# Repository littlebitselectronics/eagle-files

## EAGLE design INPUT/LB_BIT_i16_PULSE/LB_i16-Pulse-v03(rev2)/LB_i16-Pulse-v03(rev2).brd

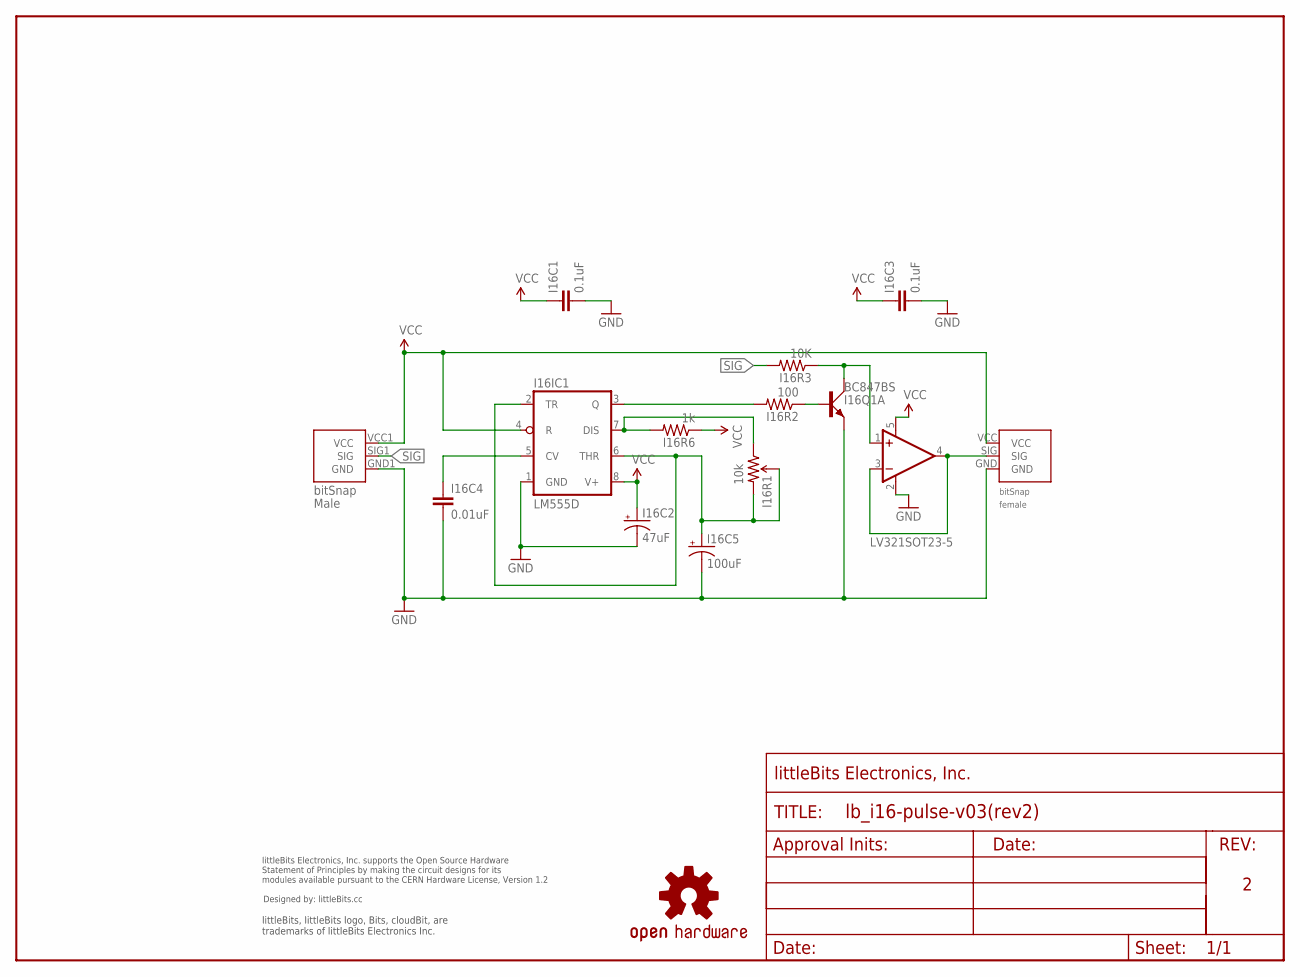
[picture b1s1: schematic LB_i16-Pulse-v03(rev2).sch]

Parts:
I16BSF1: BITSNAP_V03_FEMALE
I16BSM1: BITSNAP_V03_MALE
I16C1, I16C3: 0.1uF; 0603-CAP
I16C2: 47uF; EIA3528
I16C4: 0.01uF; 0603-CAP
I16C5: 100uF; EIA6032
I16IC1: LM555D; SO08
I16Q1: BC847BS; SOT363_PHILIPS
I16R1: 10k; TRIMPOT-3MM
I16R2: 100; 0603-RES
I16R3: 10K; 0603-RES
I16R6: 1k; 0603-RES
I16U3: LV321SOT23-5; SOT23-5
U$1: OSHWCREDIT
U$2: FRAME-LETTER-OHWOHW; FABDWG01-OHW
U$3: OSHW-LOGOL; OSHW-LOGO-L

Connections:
GND: I16BSF1.GND, I16BSM1.GND1 (GND), I16C1.2, I16C2.C (-), I16C3.2, I16C4.2, I16C5.P$2 (-), I16IC1.1 (GND), I16Q1.1 (E), I16U3.2 (V-)
unnamed: I16Q1.6 (C), I16R3.1, I16U3.1 (+IN)
unnamed: I16BSF1.SIG, I16U3.3 (-IN), I16U3.4 (OUT)
unnamed: I16IC1.3 (Q), I16R2.2
unnamed: I16Q1.2 (B), I16R2.1
unnamed: I16C4.1, I16IC1.5 (CV)
unnamed: I16IC1.7 (DIS), I16R1.1 (CCW), I16R6.2
unnamed: I16C5.P$1 (+), I16IC1.2 (TR), I16IC1.6 (THR), I16R1.2 (WIPER), I16R1.3 (CW)
SIG: I16BSM1.SIG1 (SIG), I16R3.2
VCC: I16BSF1.VCC, I16BSM1.VCC1 (VCC), I16C1.1, I16C2.A (+), I16C3.1, I16IC1.4 (R), I16IC1.8 (V+), I16R6.1, I16U3.5 (V+)

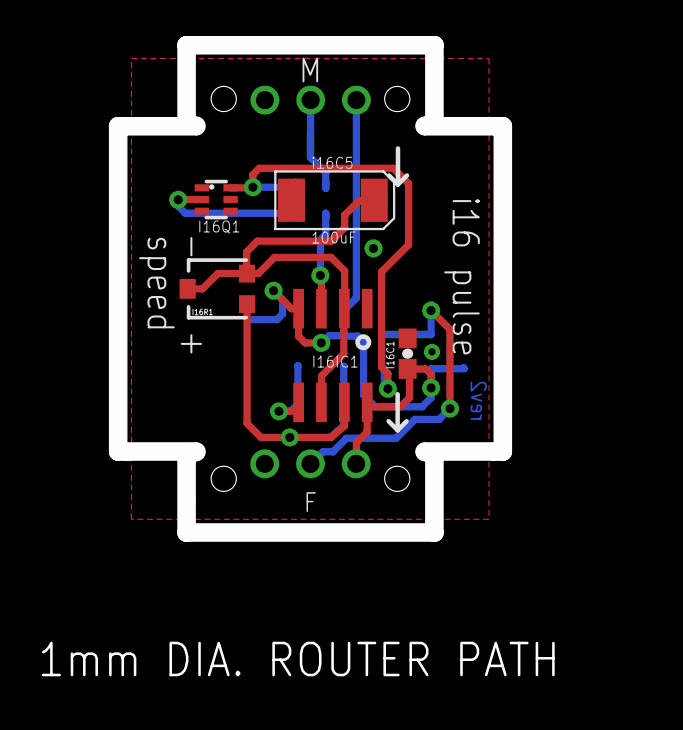
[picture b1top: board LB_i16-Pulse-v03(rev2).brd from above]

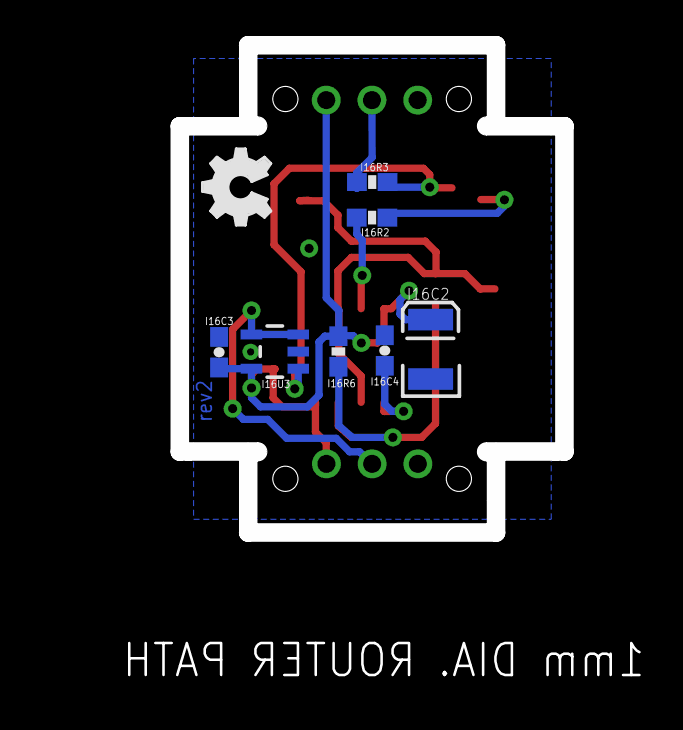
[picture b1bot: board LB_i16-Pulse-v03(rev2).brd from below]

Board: 2 copper layers, 21.4 x 27.1 mm, 18 parts (7 on the bottom side), 10 nets.

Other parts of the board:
U$20: OSHW_FILLX150_NOTEXT

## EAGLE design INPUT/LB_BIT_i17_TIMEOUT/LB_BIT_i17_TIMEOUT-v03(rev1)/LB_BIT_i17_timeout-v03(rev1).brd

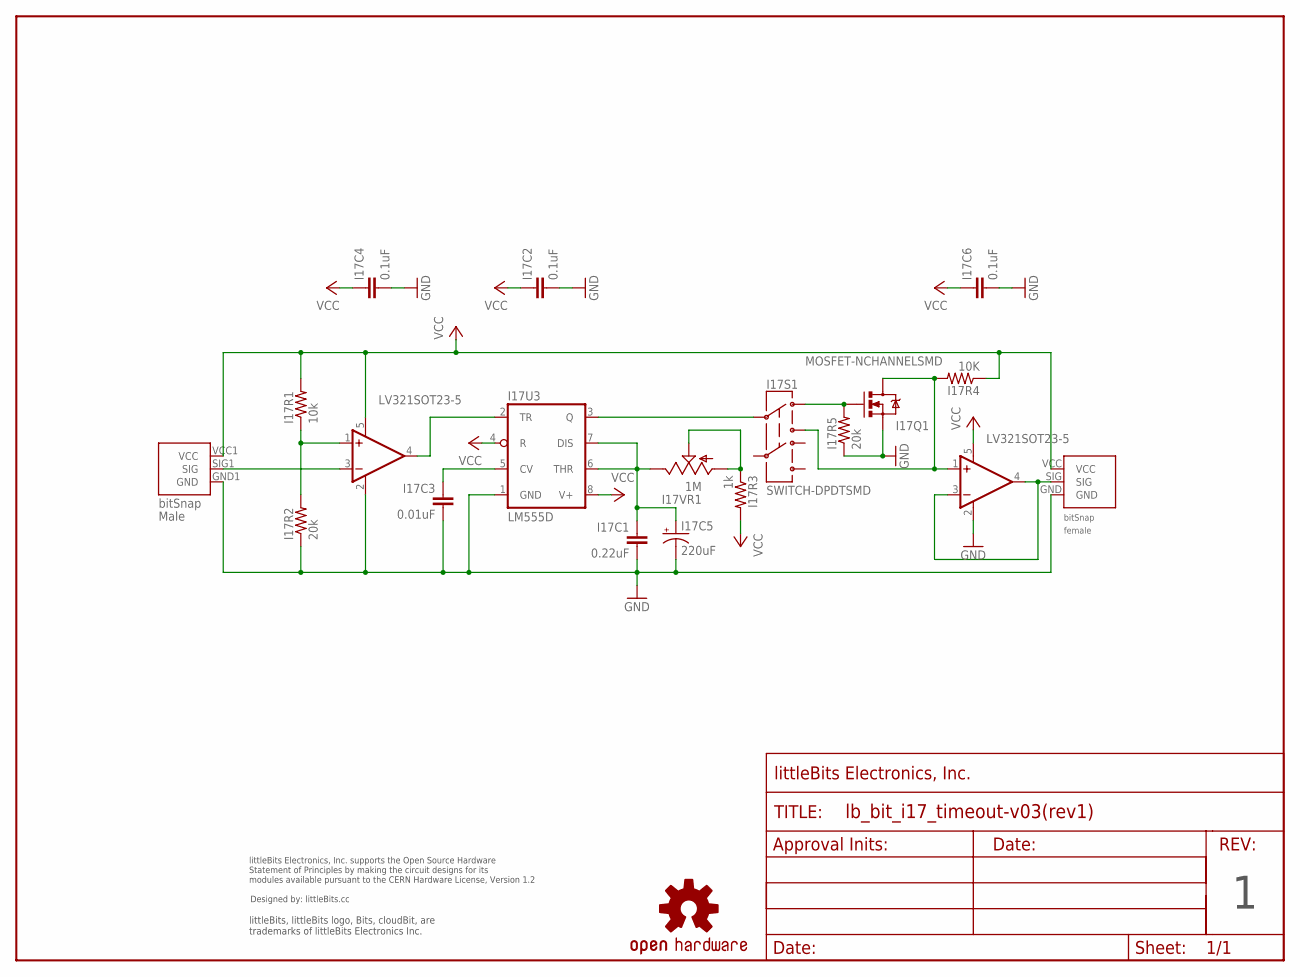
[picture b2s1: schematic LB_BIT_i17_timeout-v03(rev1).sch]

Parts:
I17BSF1: BITSNAP_V03_FEMALE
I17BSM1: BITSNAP_V03_MALE
I17C1: 0.22uF; 0603-CAP
I17C2, I17C4, I17C6: 0.1uF; 0603-CAP
I17C3: 0.01uF; 0603-CAP
I17C5: 220uF; PANASONIC_D
I17Q1: MOSFET-NCHANNELSMD; SOT23-3
I17R1: 10k; 0603-RES
I17R2, I17R5: 20k; 0603-RES
I17R3: 1k; 0603-RES
I17R4: 10K; 0603-RES
I17S1: SWITCH-DPDTSMD; AYZ0202
I17U1, I17U2: LV321SOT23-5; SOT23-5
I17U3: LM555D; SO08
I17VR1: 1M; POT-TRIM-SMD-BOURNS-3303
U$1: OSHWCREDIT
U$2: FRAME-LETTER-OHWOHW; FABDWG01-OHW
U$4: OSHW-LOGOL; OSHW-LOGO-L

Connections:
GND: I17BSF1.GND, I17BSM1.GND1 (GND), I17C1.2, I17C2.2, I17C3.2, I17C4.2, I17C5.-, I17C6.2, I17Q1.2 (S), I17R2.1, I17R5.1, I17U1.2 (V-), I17U2.2 (V-), I17U3.1 (GND)
unnamed: I17C3.1, I17U3.5 (CV)
unnamed: I17Q1.3 (D), I17R4.2, I17S1.3, I17U2.1 (+IN)
unnamed: I17Q1.1 (G), I17R5.2, I17S1.1
unnamed: I17BSM1.SIG1 (SIG), I17U1.3 (-IN)
unnamed: I17R3.1, I17VR1.1 (A), I17VR1.2 (S)
unnamed: I17S1.2, I17U3.3 (Q)
unnamed: I17BSF1.SIG, I17U2.3 (-IN), I17U2.4 (OUT)
unnamed: I17U1.4 (OUT), I17U3.2 (TR)
unnamed: I17R1.1, I17R2.2, I17U1.1 (+IN)
unnamed: I17C1.1, I17C5.+, I17U3.6 (THR), I17U3.7 (DIS), I17VR1.3 (E)
VCC: I17BSF1.VCC, I17BSM1.VCC1 (VCC), I17C2.1, I17C4.1, I17C6.1, I17R1.2, I17R3.2, I17R4.1, I17U1.5 (V+), I17U2.5 (V+), I17U3.4 (R), I17U3.8 (V+)

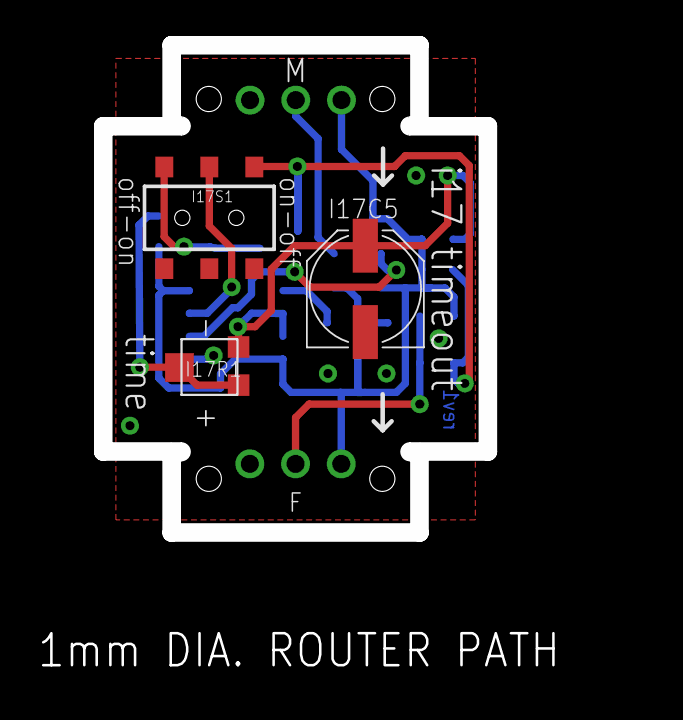
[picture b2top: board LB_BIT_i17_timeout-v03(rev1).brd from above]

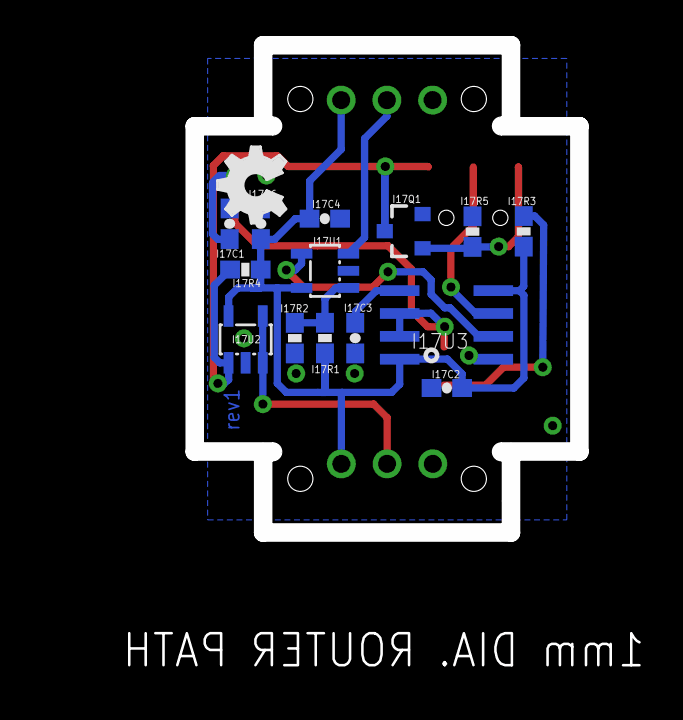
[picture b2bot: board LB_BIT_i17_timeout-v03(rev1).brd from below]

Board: 2 copper layers, 21.4 x 27.1 mm, 23 parts (14 on the bottom side), 12 nets.

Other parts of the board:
U$6: OSHW_FILLX150_NOTEXT

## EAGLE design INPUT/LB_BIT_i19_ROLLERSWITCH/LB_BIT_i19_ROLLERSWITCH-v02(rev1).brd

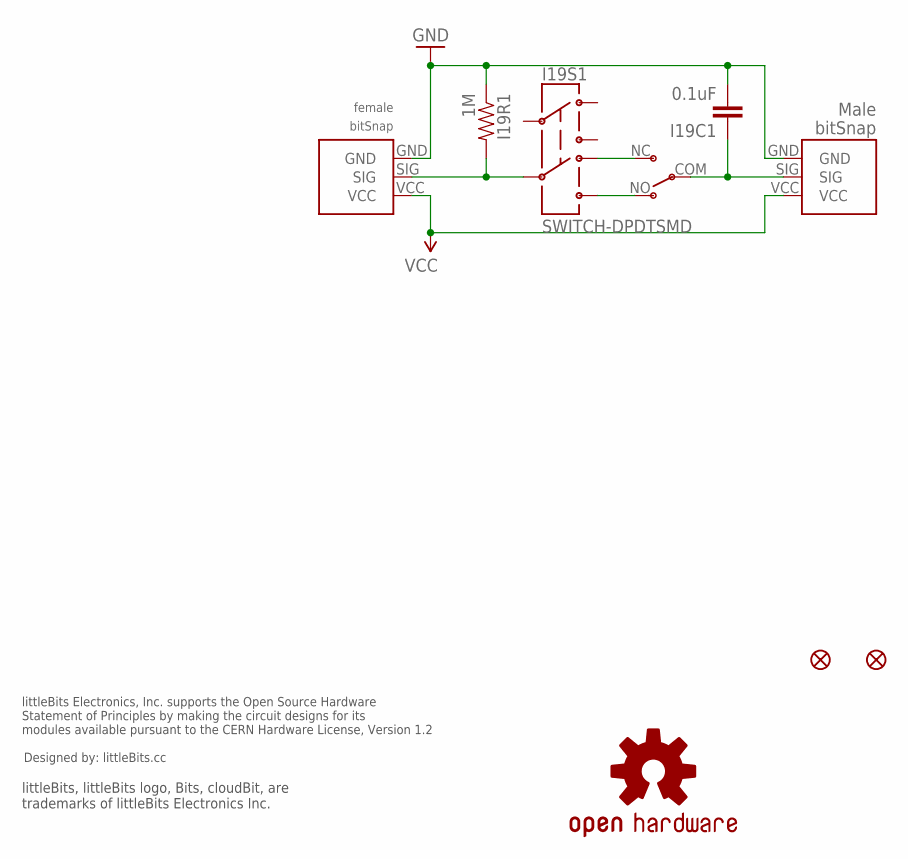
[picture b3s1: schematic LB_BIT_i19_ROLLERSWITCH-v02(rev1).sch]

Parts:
I3BSF: BITSNAP_FEMALE
I3BSM: BITSNAP_MALE
I19C1: 0.1uF; 0603-CAP
I19FD1, I19FD2: FIDUCIAL1X2; FIDUCIAL-1X2
I19R1: 1M; 0603-RES
I19S1: SWITCH-DPDTSMD; AYZ0202
I19SW2: ROLLERSWITCH-OMRON-SS-5GL2DRIGHTANGLE; ROLLERSWITCH-OMRON-D2F-01FL-A
U$1: OSHWCREDIT
U$3: OSHW-LOGOL; OSHW-LOGO-L

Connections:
GND: I3BSF.GND, I3BSM.GND, I19C1.2, I19R1.1
unnamed: I19S1.4, I19SW2.NC
unnamed: I19S1.6, I19SW2.NO
SIG: I3BSF.SIG, I19R1.2, I19S1.5
SIG2: I3BSM.SIG, I19C1.1, I19SW2.COM
VCC: I3BSF.VCC, I3BSM.VCC

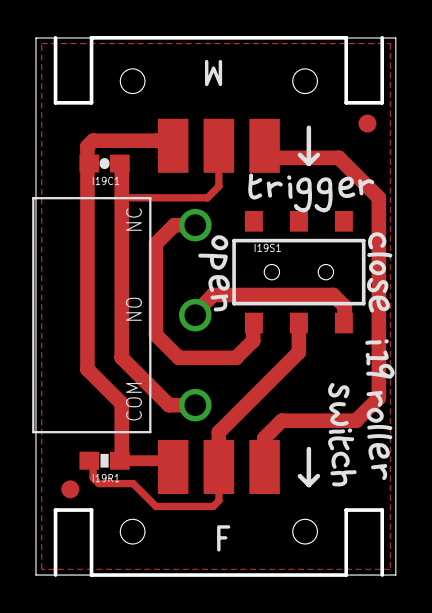
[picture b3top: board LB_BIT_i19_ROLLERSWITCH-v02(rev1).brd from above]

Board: 2 copper layers, 20.0 x 29.8 mm, 43 parts (0 on the bottom side), 6 nets.

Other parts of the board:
U$2: LB_CREDITS_V2
U$20: OSHW_FILLX150_NOTEXT
U$36, U$55: T
U$37, U$42, U$46, U$51: R
U$38, U$43, U$54: I
U$39, U$40: G
U$41, U$50, U$62, U$65: E
U$44: 1
U$45: 9
U$47, U$60, U$63: O
U$48, U$49, U$59: L
U$52, U$61: S
U$53: W
U$56, U$58: C
U$57: H
U$64: P
U$66: N

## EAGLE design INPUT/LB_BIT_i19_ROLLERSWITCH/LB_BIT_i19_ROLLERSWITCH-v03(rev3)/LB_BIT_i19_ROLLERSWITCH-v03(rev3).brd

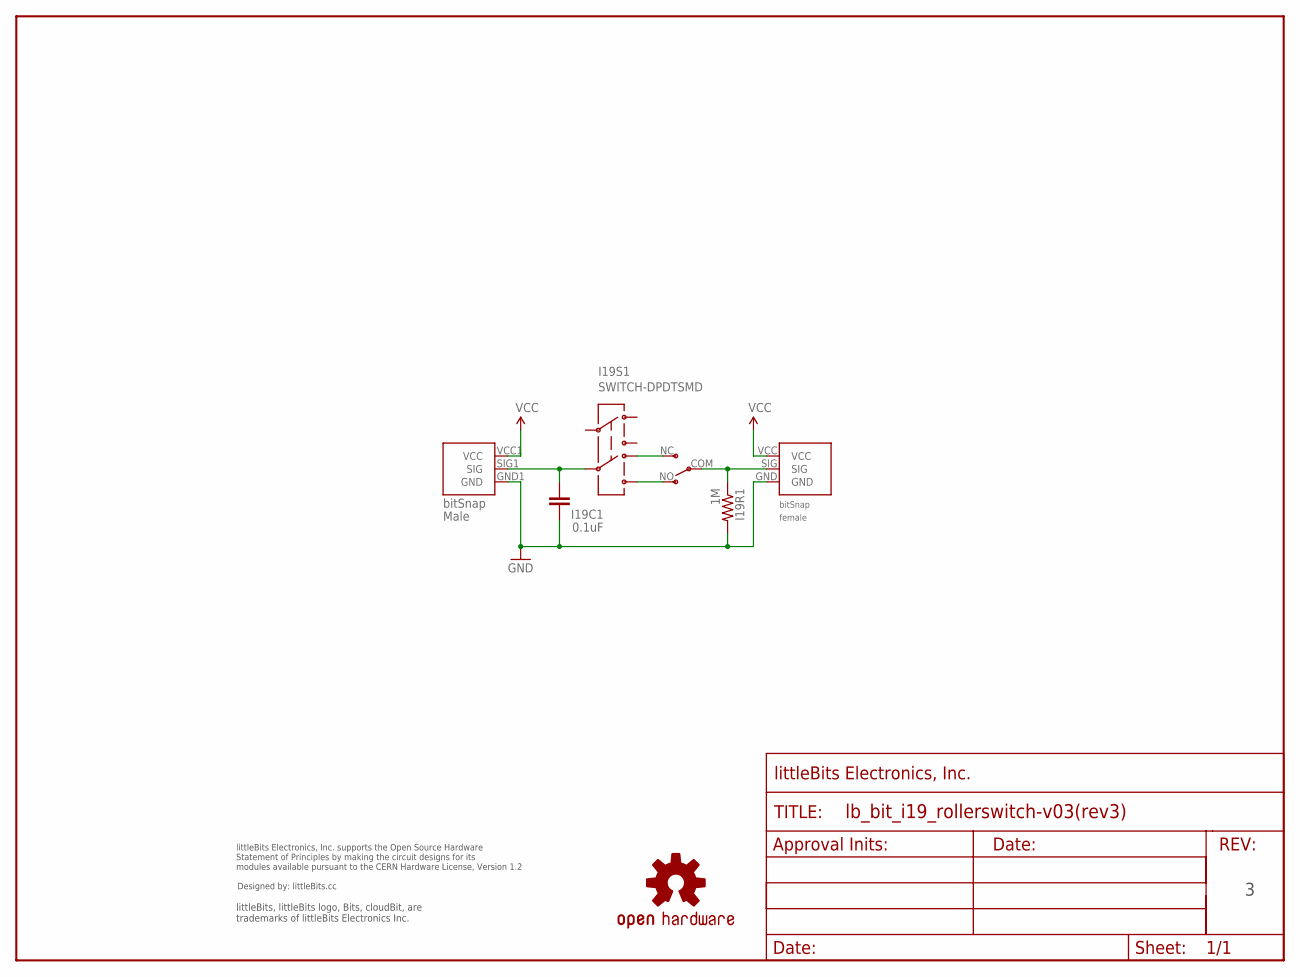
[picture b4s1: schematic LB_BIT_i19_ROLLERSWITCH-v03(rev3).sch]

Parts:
FRAME1: FRAME-LETTER-OHWOHW; FABDWG01-OHW
I19BSF1: BITSNAP_V03_FEMALE
I19BSM1: BITSNAP_V03_MALE
I19C1: 0.1uF; 0603-CAP
I19R1: 1M; 0603-RES
I19S1: SWITCH-DPDTSMD; AYZ0202
I19SW2: ROLLERSWITCH-OMRON-SS-5GL2DRIGHTANGLE; ROLLERSWITCH-OMRON-D2F-01FL-A
U$1: OSHWCREDIT
U$3: OSHW-LOGOL; OSHW-LOGO-L

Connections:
GND: I19BSF1.GND, I19BSM1.GND1 (GND), I19C1.1, I19R1.2
unnamed: I19S1.4, I19SW2.NC
unnamed: I19S1.6, I19SW2.NO
SIG: I19BSM1.SIG1 (SIG), I19C1.2, I19S1.5
SIG2: I19BSF1.SIG, I19R1.1, I19SW2.COM
VCC: I19BSF1.VCC, I19BSM1.VCC1 (VCC)

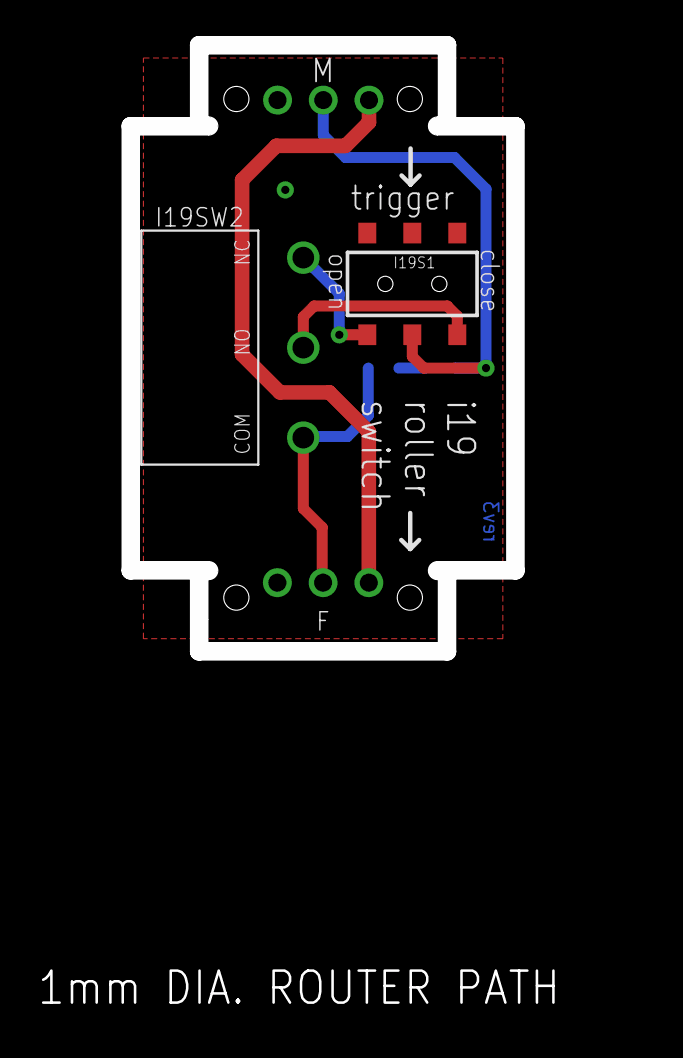
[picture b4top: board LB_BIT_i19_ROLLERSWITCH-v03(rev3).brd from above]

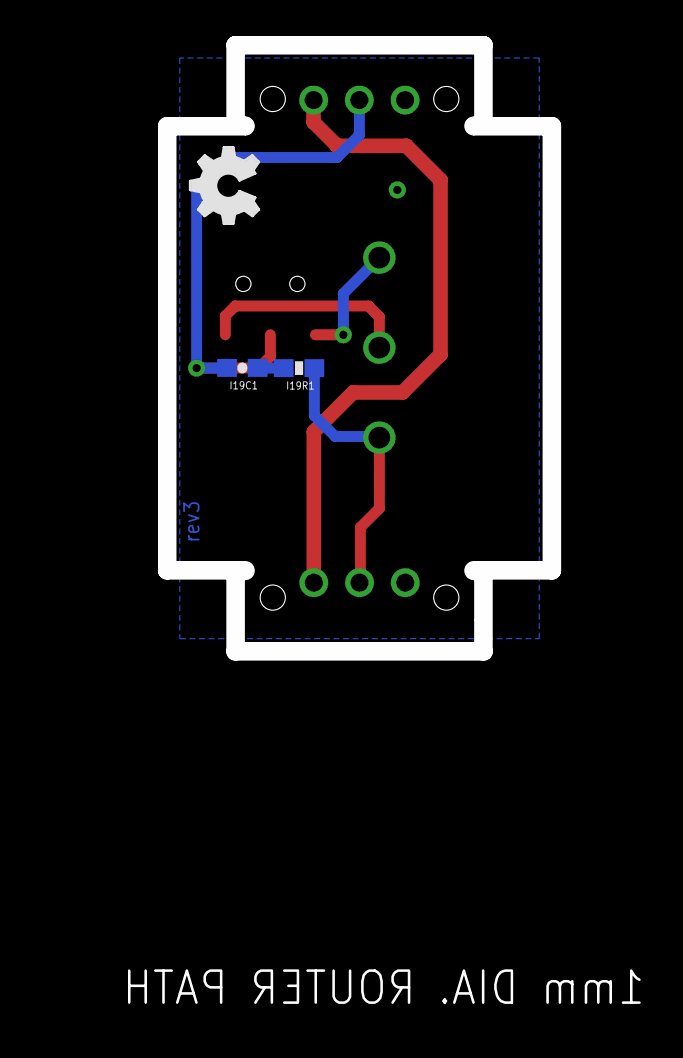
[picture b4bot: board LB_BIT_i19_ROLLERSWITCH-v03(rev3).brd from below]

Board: 2 copper layers, 21.4 x 33.7 mm, 10 parts (2 on the bottom side), 6 nets.

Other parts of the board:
U$20: OSHW_FILLX150_NOTEXT

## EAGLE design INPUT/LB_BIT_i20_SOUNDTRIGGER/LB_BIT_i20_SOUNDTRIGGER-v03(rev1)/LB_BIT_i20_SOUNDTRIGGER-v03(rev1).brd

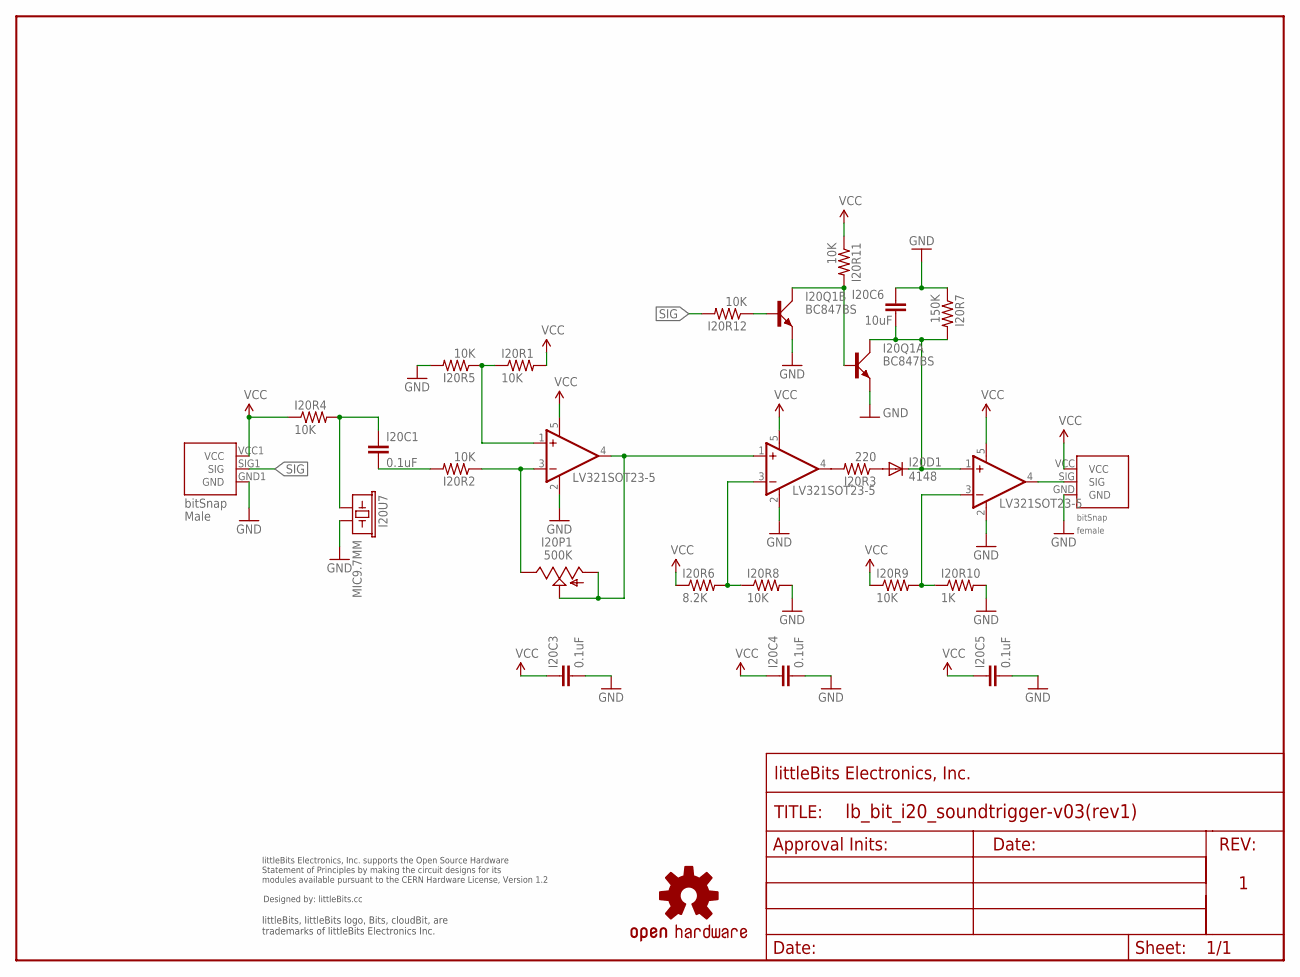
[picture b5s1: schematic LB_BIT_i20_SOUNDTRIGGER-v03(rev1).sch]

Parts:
I20BSF1: BITSNAP_V03_FEMALE
I20BSM1: BITSNAP_V03_MALE
I20C1, I20C3, I20C4, I20C5: 0.1uF; 0603-CAP
I20C6: 10uF; 0805
I20D1: 4148; SOD-323
I20P1: 500K; POT-TRIM-SMD-BOURNS-3303
I20Q1: BC847BS; SOT363_PHILIPS
I20R1, I20R2, I20R4, I20R5, I20R8, I20R9, I20R11, I20R12: 10K; 0603-RES
I20R3: 220; 0603-RES
I20R6: 8.2K; 0603-RES
I20R7: 150K; 0603-RES
I20R10: 1K; 0603-RES
I20U1, I20U2, I20U3: LV321SOT23-5; SOT23-5
I20U7: MIC9.7MM; MIC-9.7MM
U$1: OSHWCREDIT
U$5: FRAME-LETTER-OHWOHW; FABDWG01-OHW
U$29: OSHW-LOGOL; OSHW-LOGO-L

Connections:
GND: I20BSF1.GND, I20BSM1.GND1 (GND), I20C3.2, I20C4.2, I20C5.2, I20C6.1, I20Q1.1 (E), I20Q1.4 (E), I20R5.2, I20R7.1, I20R8.2, I20R10.2, I20U1.2 (V-), I20U2.2 (V-), I20U3.2 (V-), I20U7.2
unnamed: I20P1.3 (E), I20R2.1, I20U1.3 (-IN)
unnamed: I20C1.2, I20R2.2
unnamed: I20C1.1, I20R4.2, I20U7.1
unnamed: I20P1.1 (A), I20P1.2 (S), I20U1.4 (OUT), I20U2.1 (+IN)
unnamed: I20R1.1, I20R5.1, I20U1.1 (+IN)
unnamed: I20C6.2, I20D1.1 (C), I20Q1.6 (C), I20R7.2, I20U3.1 (+IN)
unnamed: I20R6.2, I20R8.1, I20U2.3 (-IN)
unnamed: I20R3.2, I20U2.4 (OUT)
unnamed: I20Q1.2 (B), I20Q1.3 (C), I20R11.2
unnamed: I20BSF1.SIG, I20U3.4 (OUT)
unnamed: I20R9.2, I20R10.1, I20U3.3 (-IN)
unnamed: I20D1.2 (A), I20R3.1
unnamed: I20Q1.5 (B), I20R12.1
SIG: I20BSM1.SIG1 (SIG), I20R12.2
VCC: I20BSF1.VCC, I20BSM1.VCC1 (VCC), I20C3.1, I20C4.1, I20C5.1, I20R1.2, I20R4.1, I20R6.1, I20R9.1, I20R11.1, I20U1.5 (V+), I20U2.5 (V+), I20U3.5 (V+)

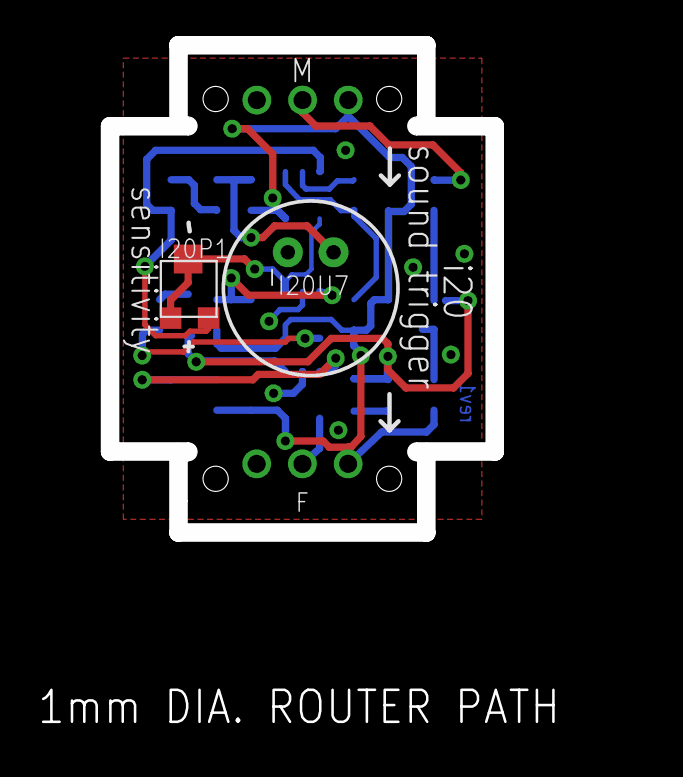
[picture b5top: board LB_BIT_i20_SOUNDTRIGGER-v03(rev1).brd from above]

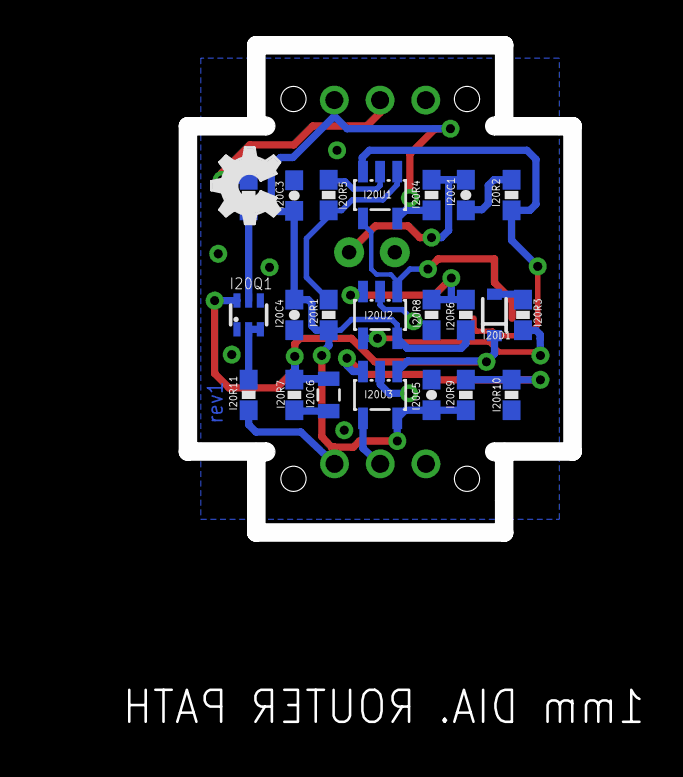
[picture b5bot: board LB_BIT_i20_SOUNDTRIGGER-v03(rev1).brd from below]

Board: 2 copper layers, 21.4 x 27.1 mm, 32 parts (22 on the bottom side), 16 nets.

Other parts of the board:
U$2: OSHW_FILLX150_NOTEXT
U$3: +
U$4: -

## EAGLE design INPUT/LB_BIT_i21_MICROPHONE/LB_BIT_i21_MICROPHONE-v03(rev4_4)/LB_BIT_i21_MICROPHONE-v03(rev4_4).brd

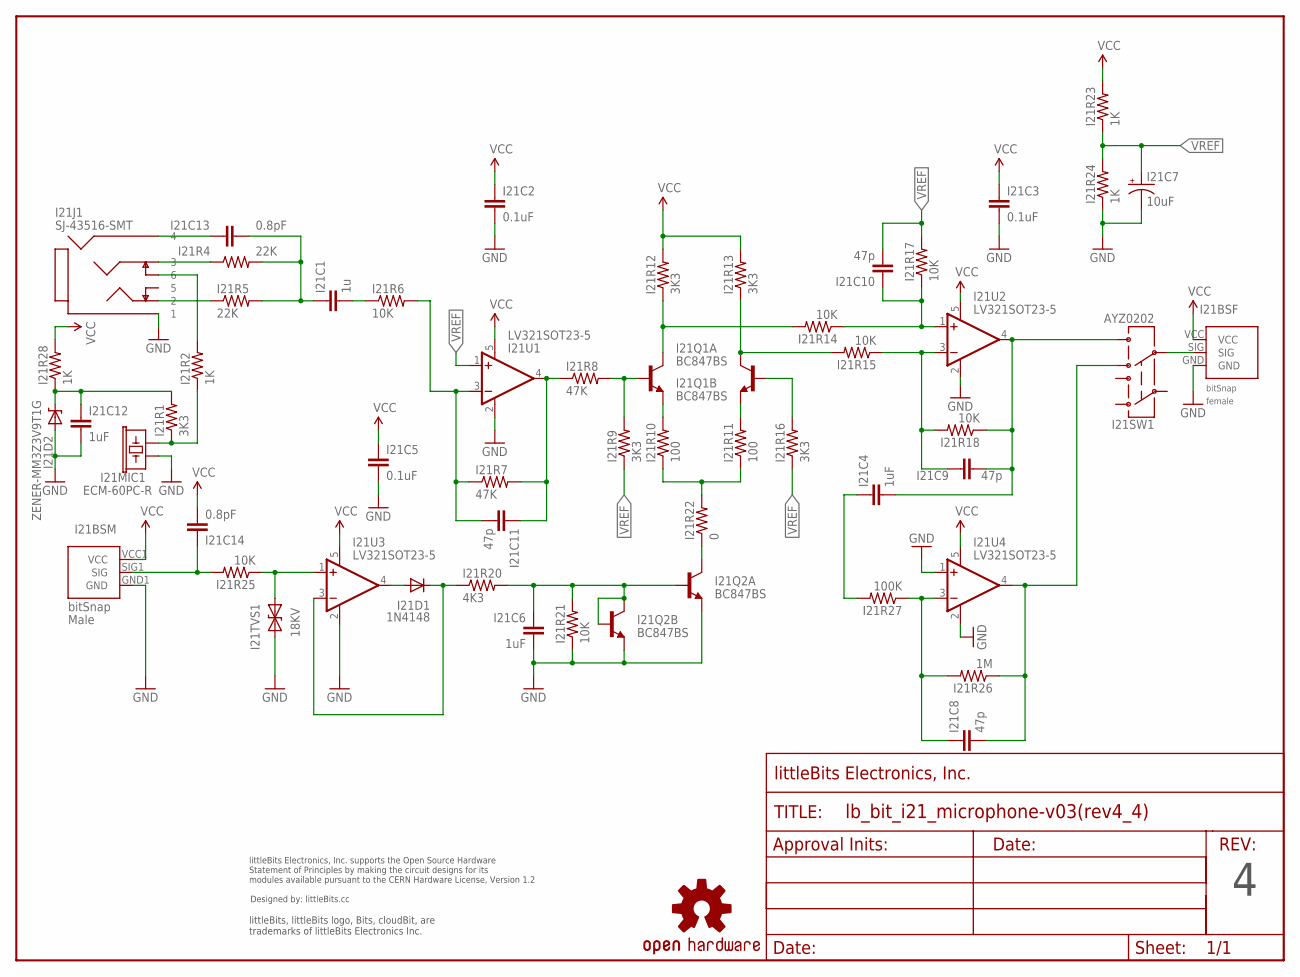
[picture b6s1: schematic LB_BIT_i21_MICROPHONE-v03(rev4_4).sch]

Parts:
I21BSF: BITSNAP_V03_FEMALE
I21BSM: BITSNAP_V03_MALE
I21C1: 1u; CAP-0603
I21C2, I21C3, I21C5: 0.1uF; CAP-0603
I21C4, I21C6, I21C12: 1uF; CAP-0603
I21C7: 10uF; EIA3216
I21C8, I21C9, I21C10, I21C11: 47p; CAP-0603
I21C13, I21C14: 0.8pF; CAP-0603
I21D1: 1N4148; SOD-323
I21D2: ZENER-MM3Z3V9T1G; SOD-323
I21J1: SJ-43516-SMT; CUI-SJ-4351
I21MIC1: ECM-60PC-R; MIC9.7MM
I21Q1, I21Q2: BC847BS; SOT-363_PHILLIPS
I21R1, I21R9, I21R12, I21R13, I21R16: 3K3; RES-0603
I21R2, I21R23, I21R24, I21R28: 1K; RES-0603
I21R4, I21R5: 22K; RES-0603
I21R6, I21R14, I21R15, I21R17, I21R18, I21R21, I21R25: 10K; RES-0603
I21R7, I21R8: 47K; RES-0603
I21R10, I21R11: 100; RES-0603
I21R20: 4K3; RES-0603
I21R22: 0; RES-0603
I21R26: 1M; RES-0603
I21R27: 100K; RES-0603
I21SW1: AYZ0202
I21TVS1: 18KV; SOD-923
I21U1, I21U2, I21U3, I21U4: LV321SOT23-5; SOT23-5
U$3: OSHWCREDIT
U$4: FRAME-LETTER-OHWOHW; FABDWG01-OHW
U$19: OSHW-LOGOL; OSHW-LOGO-L

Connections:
GND: I21BSF.GND, I21BSM.GND1 (GND), I21C2.2, I21C3.2, I21C5.2, I21C6.2, I21C7.-, I21C12.2, I21D2.2 (A), I21J1.1, I21MIC1.2, I21Q2.1 (E), I21Q2.4 (E), I21R21.1, I21R24.1, I21TVS1.1 (A), I21U1.2 (V-), I21U2.2 (V-), I21U3.2 (V-), I21U4.1 (+IN), I21U4.2 (V-)
unnamed: I21BSM.SIG1 (SIG), I21C14.1, I21R25.2
unnamed: I21D1.2 (A), I21U3.4 (OUT)
unnamed: I21D1.1 (C), I21R20.1, I21U3.3 (-IN)
unnamed: I21R25.1, I21TVS1.2 (C), I21U3.1 (+IN)
unnamed: I21C6.1, I21Q2.2 (B), I21Q2.3 (C), I21Q2.5 (B), I21R20.2, I21R21.2
unnamed: I21C13.1, I21J1.4
unnamed: I21C1.1, I21C13.2, I21R4.2, I21R5.2
unnamed: I21C1.2, I21R6.1
unnamed: I21J1.6, I21R2.2
unnamed: I21MIC1.1, I21R1.1, I21R2.1
unnamed: I21C11.2, I21R6.2, I21R7.1, I21U1.3 (-IN)
unnamed: I21C11.1, I21R7.2, I21R8.1, I21U1.4 (OUT)
unnamed: I21Q1.2 (B), I21R8.2, I21R9.2
unnamed: I21Q1.1 (E), I21R10.2
unnamed: I21Q1.4 (E), I21R11.2
unnamed: I21R10.1, I21R11.1, I21R22.2
unnamed: I21J1.2, I21R5.1
unnamed: I21Q1.3 (C), I21R13.1, I21R15.2
unnamed: I21Q1.5 (B), I21R16.2
unnamed: I21Q1.6 (C), I21R12.1, I21R14.2
unnamed: I21C10.1, I21R14.1, I21R17.1, I21U2.1 (+IN)
unnamed: I21C9.1, I21R15.1, I21R18.2, I21U2.3 (-IN)
unnamed: I21C4.2, I21C9.2, I21R18.1, I21SW1.6, I21U2.4 (OUT)
unnamed: I21Q2.6 (C), I21R22.1
unnamed: I21BSF.SIG, I21SW1.5
unnamed: I21J1.3, I21R4.1
unnamed: I21C8.1, I21R26.2, I21R27.1, I21U4.3 (-IN)
unnamed: I21C8.2, I21R26.1, I21SW1.4, I21U4.4 (OUT)
unnamed: I21C4.1, I21R27.2
unnamed: I21C12.1, I21D2.1 (C), I21R1.2, I21R28.1
VCC: I21BSF.VCC, I21BSM.VCC1 (VCC), I21C2.1, I21C3.1, I21C5.1, I21C14.2, I21R12.2, I21R13.2, I21R23.2, I21R28.2, I21U1.5 (V+), I21U2.5 (V+), I21U3.5 (V+), I21U4.5 (V+)
VREF: I21C7.+, I21C10.2, I21R9.1, I21R16.1, I21R17.2, I21R23.1, I21R24.2, I21U1.1 (+IN)

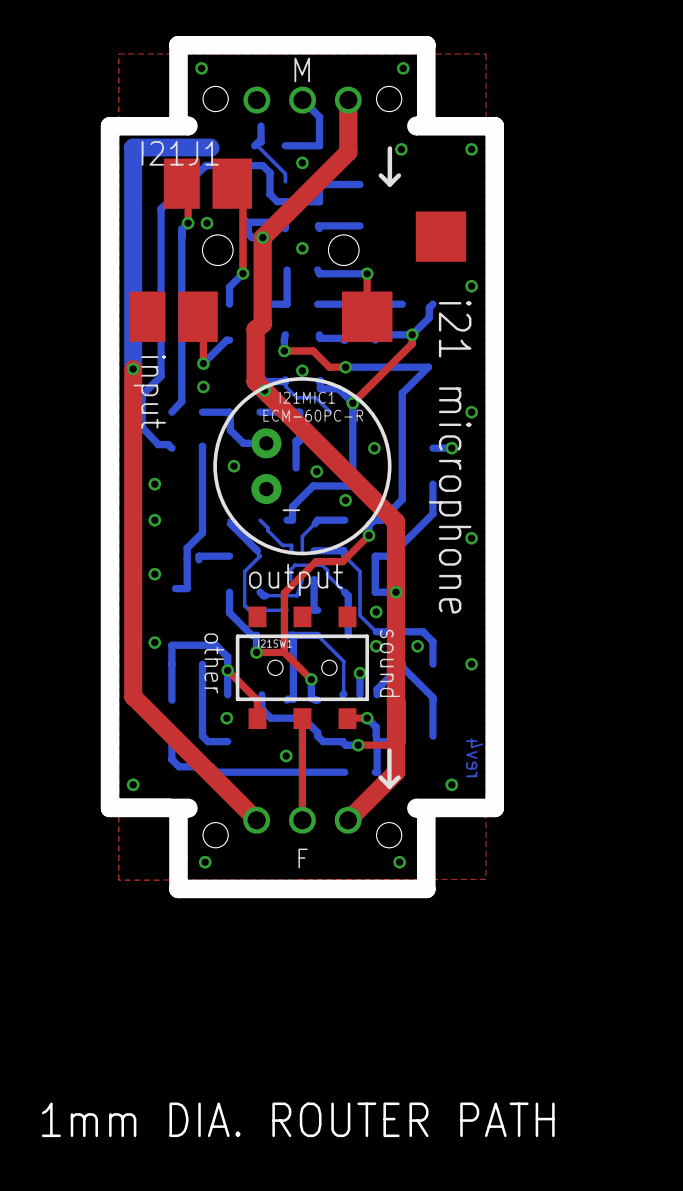
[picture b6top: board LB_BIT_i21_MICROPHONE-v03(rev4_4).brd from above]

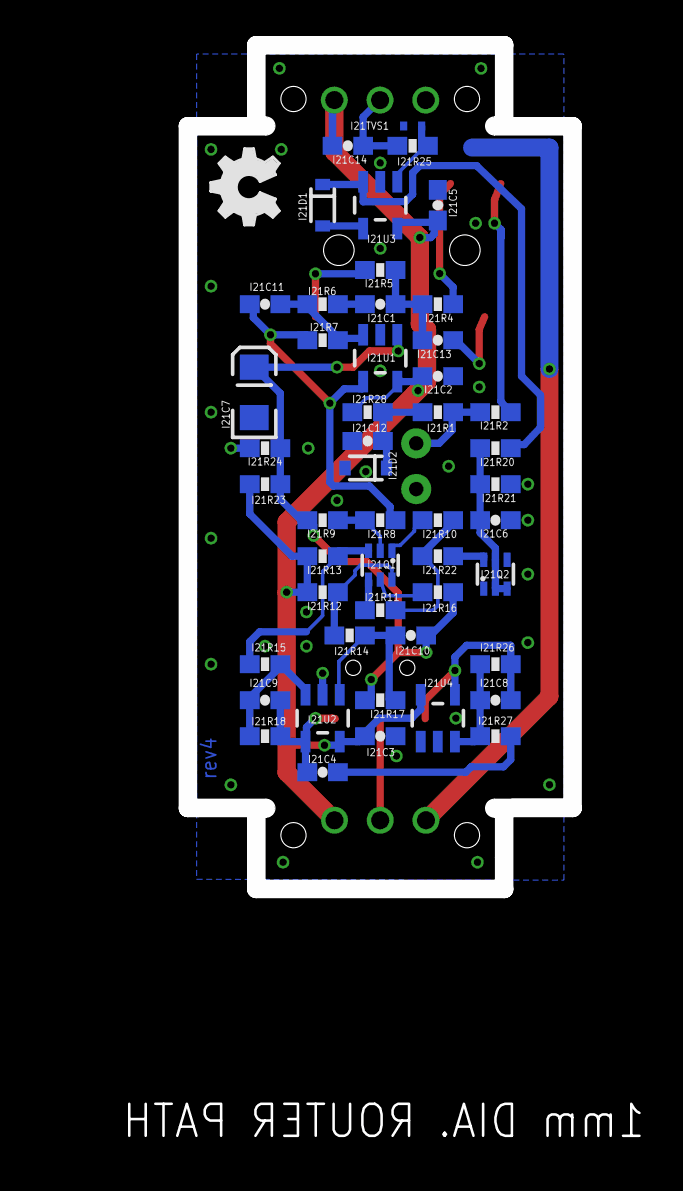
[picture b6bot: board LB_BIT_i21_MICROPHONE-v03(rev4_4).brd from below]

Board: 2 copper layers, 21.4 x 46.9 mm, 58 parts (49 on the bottom side), 33 nets.

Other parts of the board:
U$8: OSHW_FILLX150_NOTEXT

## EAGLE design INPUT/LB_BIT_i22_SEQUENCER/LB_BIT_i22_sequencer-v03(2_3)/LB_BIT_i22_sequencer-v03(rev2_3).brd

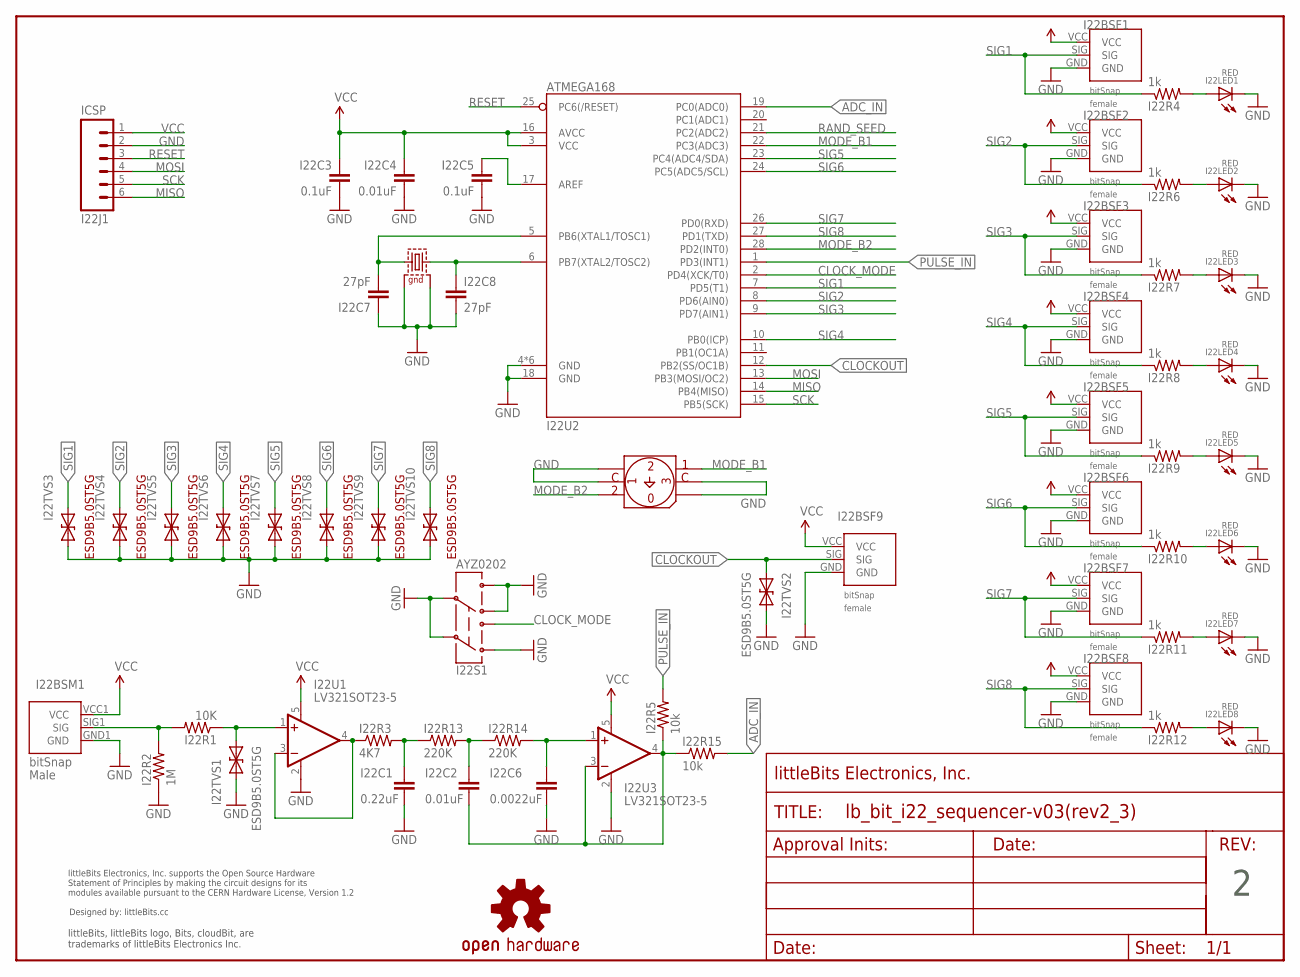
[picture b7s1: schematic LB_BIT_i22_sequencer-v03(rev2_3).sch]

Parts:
I22BSF1, I22BSF2, I22BSF3, I22BSF4, I22BSF5, I22BSF6, I22BSF7, I22BSF8, I22BSF9: BITSNAP_V03_FEMALE
I22BSM1: BITSNAP_V03_MALE
I22C1: 0.22uF; CAP-0603
I22C2, I22C4: 0.01uF; CAP-0603
I22C3, I22C5: 0.1uF; CAP-0603
I22C6: 0.0022uF; CAP-0603
I22C7, I22C8: 27pF; CAP-0603
I22J1: ICSP; SIP6-SM-0.1IN-NOS.S.
I22LED1, I22LED2, I22LED3, I22LED4, I22LED5, I22LED6, I22LED7, I22LED8: RED; LED-1206
I22Q1: 8MHz; CRYSTAL-SMD-7B-SERIES-5X3.2MM
I22R1: 10K; RES-0603
I22R2: 1M; RES-0603
I22R3: 4K7; RES-0603
I22R4, I22R6, I22R7, I22R8, I22R9, I22R10, I22R11, I22R12: 1k; RES-0603
I22R5, I22R15: 10k; RES-0603
I22R13, I22R14: 220K; RES-0603
I22S1: AYZ0202
I22S2: TER-04S
I22TVS1, I22TVS2: ESD9B5.0ST5G; SOD-923
I22TVS3, I22TVS4, I22TVS5, I22TVS6, I22TVS7, I22TVS8, I22TVS9, I22TVS10: DIODE-TVSSOD-923; SOD-923
I22U1, I22U3: LV321SOT23-5; SOT23-5
I22U2: ATMEGA168; VQFN28
U$11: OSHW-LOGOL; OSHW-LOGO-L
U$14: FRAME-LETTER-OHWOHW; FABDWG01-OHW
U$15: OSHWCREDIT

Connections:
ADC_IN: I22R15.2, I22U2.19 (PC0(ADC0))
CLOCKOUT: I22BSF9.SIG, I22TVS2.1 (A), I22U2.12 (PB2(SS/OC1B))
CLOCK_MODE: I22S1.3, I22U2.2 (PD4(XCK/T0))
GND: I22BSF1.GND, I22BSF2.GND, I22BSF3.GND, I22BSF4.GND, I22BSF5.GND, I22BSF6.GND, I22BSF7.GND, I22BSF8.GND, I22BSF9.GND, I22BSM1.GND1 (GND), I22C1.2, I22C3.2, I22C4.2, I22C5.2, I22C6.2, I22C7.1, I22C8.2, I22J1.2, I22LED1.C, I22LED2.C, I22LED3.C, I22LED4.C, I22LED5.C, I22LED6.C, I22LED7.C, I22LED8.C, I22Q1.P$2 (2), I22Q1.P$4 (4), I22R2.1, I22S1.1, I22S1.2, I22S1.4, I22S1.5, I22S1.6, I22S2.P1, I22S2.P2, I22S2.P4, I22S2.P5, I22TVS1.1 (A), I22TVS2.2 (C), I22TVS3.1 (A), I22TVS4.1 (A), I22TVS5.1 (A), I22TVS6.1 (A), I22TVS7.1 (A), I22TVS8.1 (A), I22TVS9.1 (A), I22TVS10.1 (A), I22U1.2 (V-), I22U2.4 (GND), I22U2.18 (GND), I22U2.TH (GND), I22U2.TH@1 (GND), I22U2.TH@2 (GND), I22U2.TH@3 (GND), I22U2.TH@4 (GND), I22U3.2 (V-)
MISO: I22J1.6, I22U2.14 (PB4(MISO))
MODE_B1: I22S2.P6, I22U2.22 (PC3(ADC3))
MODE_B2: I22S2.P3, I22U2.28 (PD2(INT0))
MOSI: I22J1.4, I22U2.13 (PB3(MOSI/OC2))
unnamed: I22C5.1, I22U2.17 (AREF)
unnamed: I22C7.2, I22Q1.P$1 (1), I22U2.5 (PB6(XTAL1/TOSC1))
unnamed: I22C2.2, I22R5.1, I22R15.1, I22U3.3 (-IN), I22U3.4 (OUT)
unnamed: I22R3.1, I22U1.3 (-IN), I22U1.4 (OUT)
unnamed: I22C2.1, I22R13.2, I22R14.1
unnamed: I22C8.1, I22Q1.P$3 (3), I22U2.6 (PB7(XTAL2/TOSC2))
unnamed: I22C6.1, I22R14.2, I22U3.1 (+IN)
unnamed: I22C1.1, I22R3.2, I22R13.1
unnamed: I22LED1.A, I22R4.2
unnamed: I22LED2.A, I22R6.2
unnamed: I22LED3.A, I22R7.2
unnamed: I22LED4.A, I22R8.2
unnamed: I22LED5.A, I22R9.2
unnamed: I22LED6.A, I22R10.2
unnamed: I22LED7.A, I22R11.2
unnamed: I22LED8.A, I22R12.2
unnamed: I22R1.1, I22TVS1.2 (C), I22U1.1 (+IN)
PULSE_IN: I22R5.2, I22U2.1 (PD3(INT1))
RAND_SEED: I22U2.21 (PC2(ADC2))
RESET: I22J1.3, I22U2.25 (PC6(/RESET))
SCK: I22J1.5, I22U2.15 (PB5(SCK))
SIG: I22BSM1.SIG1 (SIG), I22R1.2, I22R2.2
SIG1: I22BSF1.SIG, I22R4.1, I22TVS3.2 (C), I22U2.7 (PD5(T1))
SIG2: I22BSF2.SIG, I22R6.1, I22TVS4.2 (C), I22U2.8 (PD6(AIN0))
SIG3: I22BSF3.SIG, I22R7.1, I22TVS5.2 (C), I22U2.9 (PD7(AIN1))
SIG4: I22BSF4.SIG, I22R8.1, I22TVS6.2 (C), I22U2.10 (PB0(ICP))
SIG5: I22BSF5.SIG, I22R9.1, I22TVS7.2 (C), I22U2.23 (PC4(ADC4/SDA))
SIG6: I22BSF6.SIG, I22R10.1, I22TVS8.2 (C), I22U2.24 (PC5(ADC5/SCL))
SIG7: I22BSF7.SIG, I22R11.1, I22TVS9.2 (C), I22U2.26 (PD0(RXD))
SIG8: I22BSF8.SIG, I22R12.1, I22TVS10.2 (C), I22U2.27 (PD1(TXD))
VCC: I22BSF1.VCC, I22BSF2.VCC, I22BSF3.VCC, I22BSF4.VCC, I22BSF5.VCC, I22BSF6.VCC, I22BSF7.VCC, I22BSF8.VCC, I22BSF9.VCC, I22BSM1.VCC1 (VCC), I22C3.1, I22C4.1, I22J1.1, I22U1.5 (V+), I22U2.3 (VCC), I22U2.16 (AVCC), I22U3.5 (V+)

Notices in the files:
parts and their libraries:
SparkFun: Licensing: CC v3.0 Share-Alike You are welcome to use this library for commercial purposes.
LITTLEBITS: modules available pursuant to the CERN Hardware License,
Version 1.2
LITTLEBITS: modules available pursuant to the CERN Hardware License, Version 1.2
